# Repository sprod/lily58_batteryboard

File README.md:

# Batteryboard for the Lily58

This is a custom designed pcb for the lily58 keyboard. It allows to have a wireless keyboard with the battery plugable and a switch to turn it on/off.

Following components are used:

JST Molex 1,25mm Pitch SMD
https://aliexpress.com/item/32804521041.html?spm=a2g0o.order_list.order_list_main.22.7a145c5fKYKLOW&gatewayAdapt=glo2deu

spdt MSK-12C02 smd 
https://aliexpress.com/item/4000685483225.html?spm=a2g0o.productlist.main.1.684339623njpeG&algo_pvid=c371b2d0-1737-4305-bab2-7dc4363c04ca&utparam-url=scene%3Asearch%7Cquery_from%3A

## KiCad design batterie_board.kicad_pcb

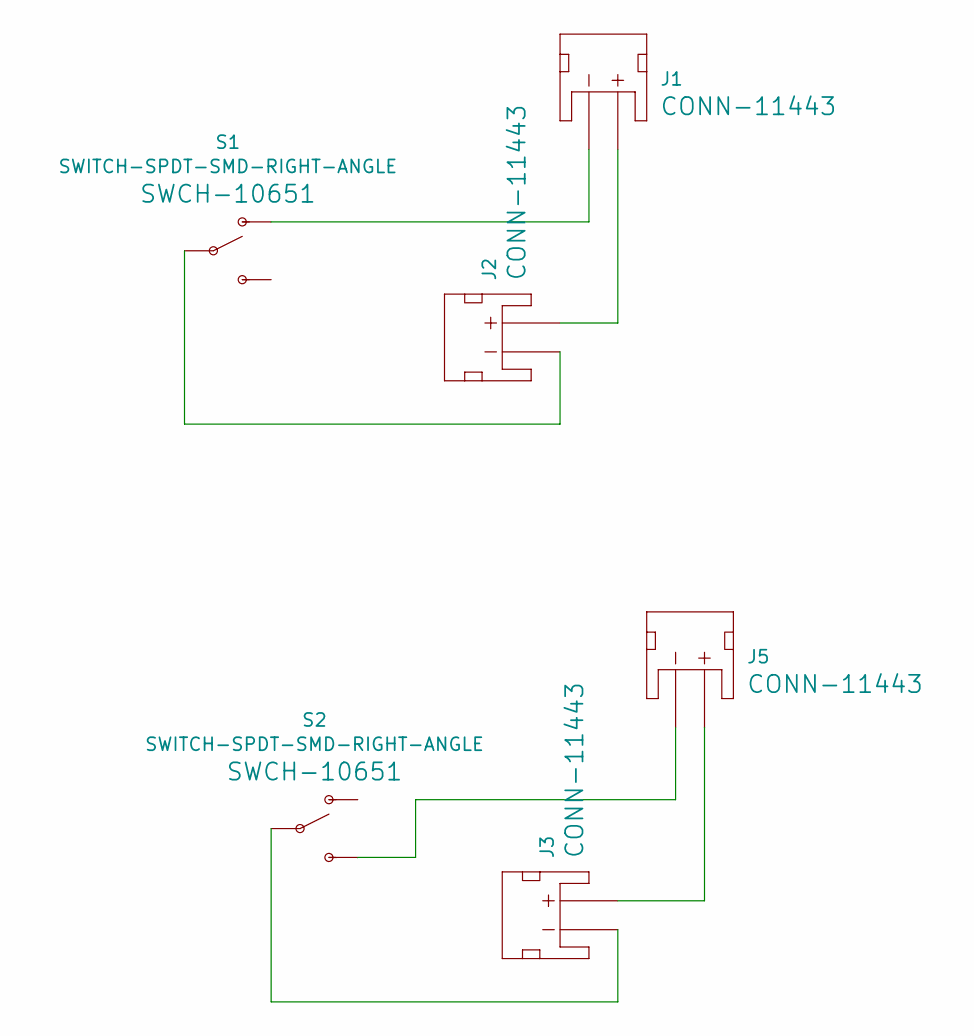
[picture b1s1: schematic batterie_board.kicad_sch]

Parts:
J1, J2, J3, J5: JST_2MM_MALE; JST-2-SMD
S1, S2: SWITCH-SPDT-SMD-RIGHT-ANGLE; SWITCH_SPST_SMD_A

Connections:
unnamed: J1.2 (+), J2.2 (+)
unnamed: J1.1 (-), S1.1 (O)
unnamed: J3.2 (+), J5.2 (+)
unnamed: J5.1 (-), S2.3 (S)
unnamed: J2.1 (-), S1.2
unnamed: J3.1 (-), S2.2

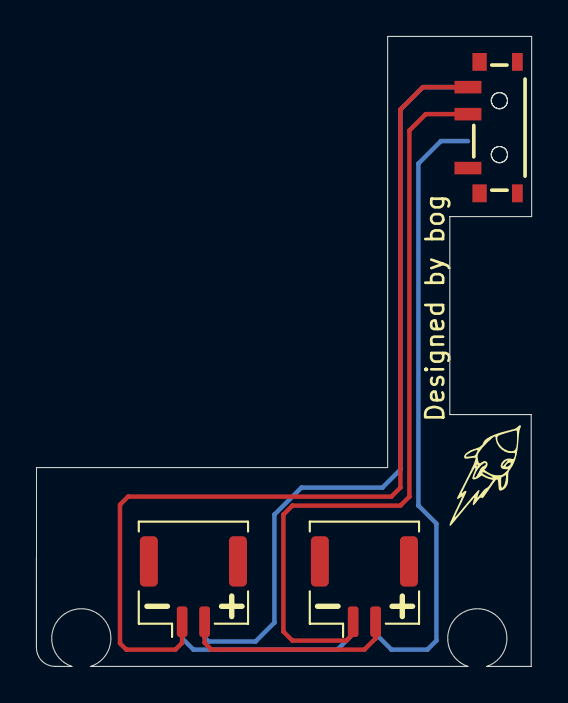
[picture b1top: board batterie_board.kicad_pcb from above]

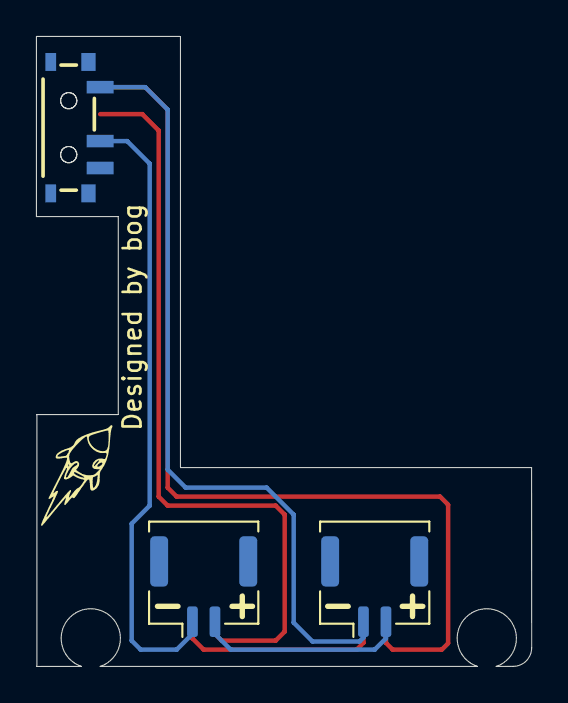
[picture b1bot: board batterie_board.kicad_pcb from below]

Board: 2 copper layers, 27.5 x 35.0 mm, 6 parts (3 on the bottom side), 6 nets.

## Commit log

2024-01-20 init upload
2024-01-20 cleanup
